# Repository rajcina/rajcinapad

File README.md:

# Rajcinapad
rajcinapad is a six key macropad with a rotary encoder and lights
it is a project i made for hackclub blueprint

# Features
- It has a rotary encoder switch that can change volume 
 i also use it to change the leds
- the pcb looks cool

# BOM
- 6x Cherry MX Switches
- 6x DSA Keycaps
- 1x EC11 Rotary encoder switch
- 4x SK6812 MINI neopixels
- 1x XIAO RP2040
- 1x Case (2 parts)
- 4x M3x16mm screws

# Pictures
## PCB

## Case

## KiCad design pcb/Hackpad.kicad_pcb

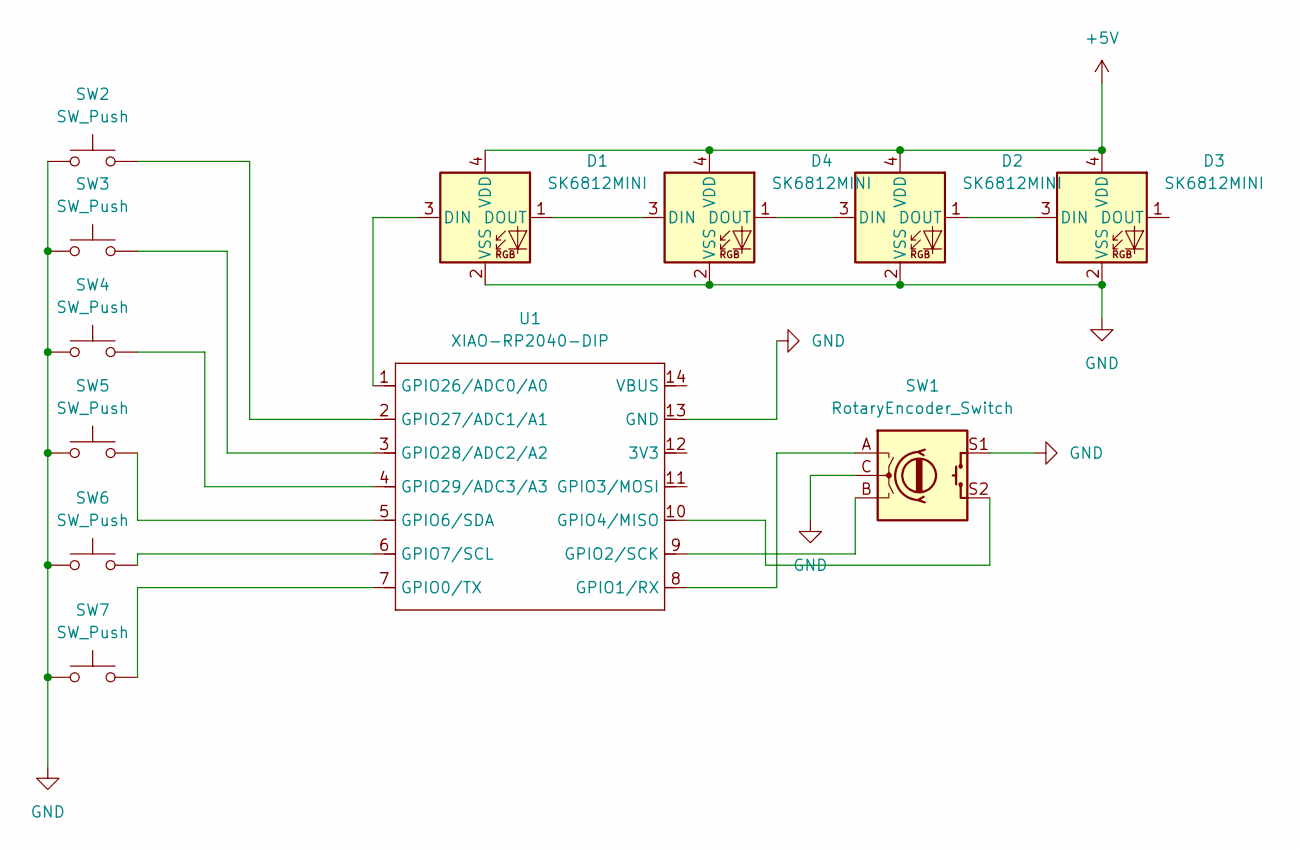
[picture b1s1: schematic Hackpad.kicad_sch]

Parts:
D1, D2, D3, D4: SK6812MINI; LED_SK6812MINI_PLCC4_3.5x3.5mm_P1.75mm
SW1: RotaryEncoder_Switch; RotaryEncoder_Alps_EC11E-Switch_Vertical_H20mm
SW2, SW3, SW4, SW5, SW6, SW7: SW_Push; SW_Cherry_MX_1.00u_PCB
U1: XIAO-RP2040-DIP

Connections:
+5V: D1.4 (VDD), D2.4 (VDD), D3.4 (VDD), D4.4 (VDD), U1.14 (VBUS)
GND: D1.2 (VSS), D2.2 (VSS), D3.2 (VSS), D4.2 (VSS), SW1.C, SW1.S1, SW2.1, SW3.1, SW4.1, SW5.1, SW6.1, SW7.1, U1.13 (GND)
unnamed: D1.3 (DIN), U1.1 (GPIO26/ADC0/A0)
unnamed: D1.1 (DOUT), D4.3 (DIN)
unnamed: D2.3 (DIN), D4.1 (DOUT)
unnamed: D2.1 (DOUT), D3.3 (DIN)
unnamed: SW7.2, U1.7 (GPIO0/TX)
unnamed: SW1.A, U1.8 (GPIO1/RX)
unnamed: SW1.B, U1.9 (GPIO2/SCK)
unnamed: SW1.S2, U1.10 (GPIO4/MISO)
unnamed: SW5.2, U1.5 (GPIO6/SDA)
unnamed: SW6.2, U1.6 (GPIO7/SCL)
unnamed: SW2.2, U1.2 (GPIO27/ADC1/A1)
unnamed: SW3.2, U1.3 (GPIO28/ADC2/A2)
unnamed: SW4.2, U1.4 (GPIO29/ADC3/A3)

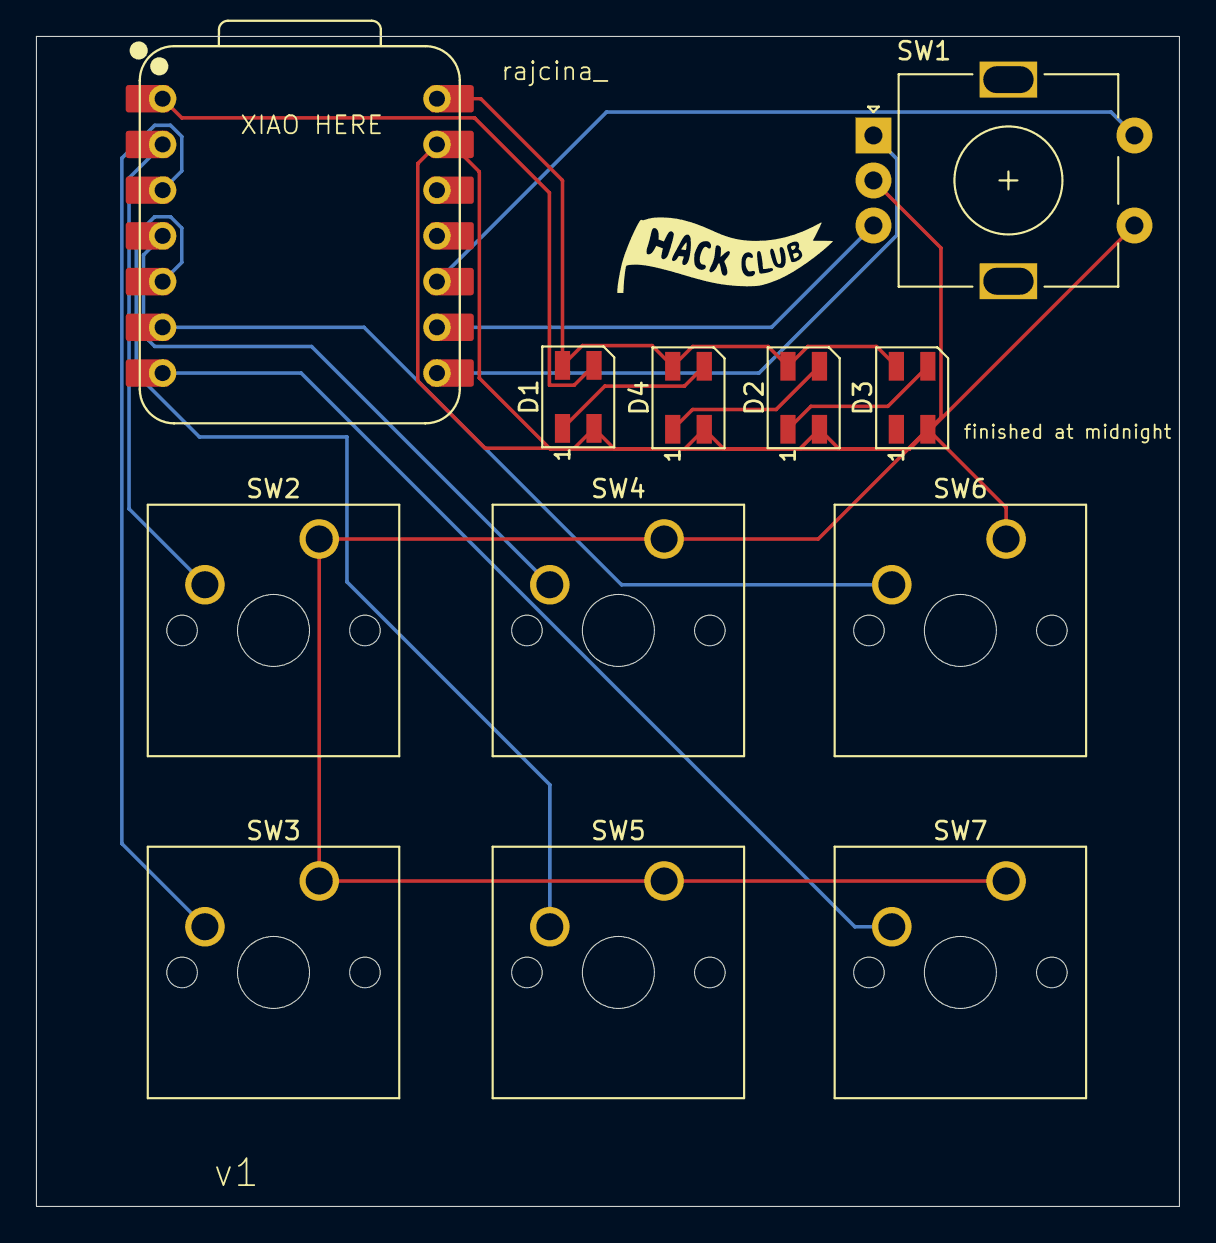
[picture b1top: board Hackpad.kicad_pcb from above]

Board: 2 copper layers, 63.5 x 65.0 mm, 12 parts (0 on the bottom side), 15 nets.

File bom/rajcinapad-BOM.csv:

"Reference","Qty","Value","DNP","Exclude from BOM","Exclude from Board","Footprint","Datasheet"
"D1,D2,D3,D4","4","SK6812MINI","","","","LED_SMD:LED_SK6812MINI_PLCC4_3.5x3.5mm_P1.75mm","https://cdn-shop.adafruit.com/product-files/2686/SK6812MINI_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"
"SW1","1","RotaryEncoder_Switch","","","","Rotary_Encoder:RotaryEncoder_Alps_EC11E-Switch_Vertical_H20mm","~"
"SW2,SW3,SW4,SW5,SW6,SW7","6","SW_Push","","","","Button_Switch_Keyboard:SW_Cherry_MX_1.00u_PCB","~"
"U1","1","XIAO-RP2040-DIP","","","","OPL:XIAO-RP2040-DIP",""

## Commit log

2025-12-11 Added firmware
2025-12-11 Uploaded pictures
2025-12-11 added pcb
2025-12-11 added gerbers
2025-12-12 added case
2025-12-12 added bill of materials
2025-12-13 fixed neopixels not having power
2025-12-13 Create LICENSE
